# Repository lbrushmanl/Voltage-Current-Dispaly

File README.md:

# Voltage-Current-Dispaly
This project was based around using the 11-digit VFD displays that you can buy for cheap at Jaycar 
https://www.jaycar.co.nz/11-digit-fluoro-display-bargain/p/ZD1880?pos=1&queryId=efb51b3d6997d6bc33e34b690ac22e3b&sort=relevance&searchText=11%20Digit%20Fluoro%20Display%20Bargain

As these displays look cool, I came up with the idea of making a voltage current display that I could then use for lots of my other projects. 
The first 5 digits would be voltage and the last 5 for current leaving the centre one blank.

To drive the display, a voltage of around 4.5V is needed for the filament, and 12V is needed for grids and digits. The 4.5V came from an LM317 adjustable voltage regulator.
The board was designed to use an ATMega8, as I had a few from UNI. 

The display was driven via shift registers and a 7seg decoder, as this would only require three GPIO pins on the MCU to be used. It also seemed like a cool idea.

Due to this driver circuitry, the following data structure was formed.

The first 4 bits are the BCD value that the 7seg decoder will read, the 5th bit is the decimal point, and bits 6 to 15 are the grids of the VFD.
A B C D DP G1 G2 G3 G4 G5 G7 G8 G9 G10 G11

I assembled one board fully and found out that a few things were wrong. I also used my ATMegaU4 dev board for testing rather than the ATMega8, as it was easier to use
The main thing I found wrong was the C segment was connected to the comma. I also found out that the Blanking pin of the decoder was connected high rather than low. The biggest issue was that the display was the wrong way around. Flipping it fixed the problem however it no longer looks as good.

View of the test setup

Initial test after fixing the PCB showing 0 and the dot

The first numbers are quite dim

Finaly brighter and the ADC is conected

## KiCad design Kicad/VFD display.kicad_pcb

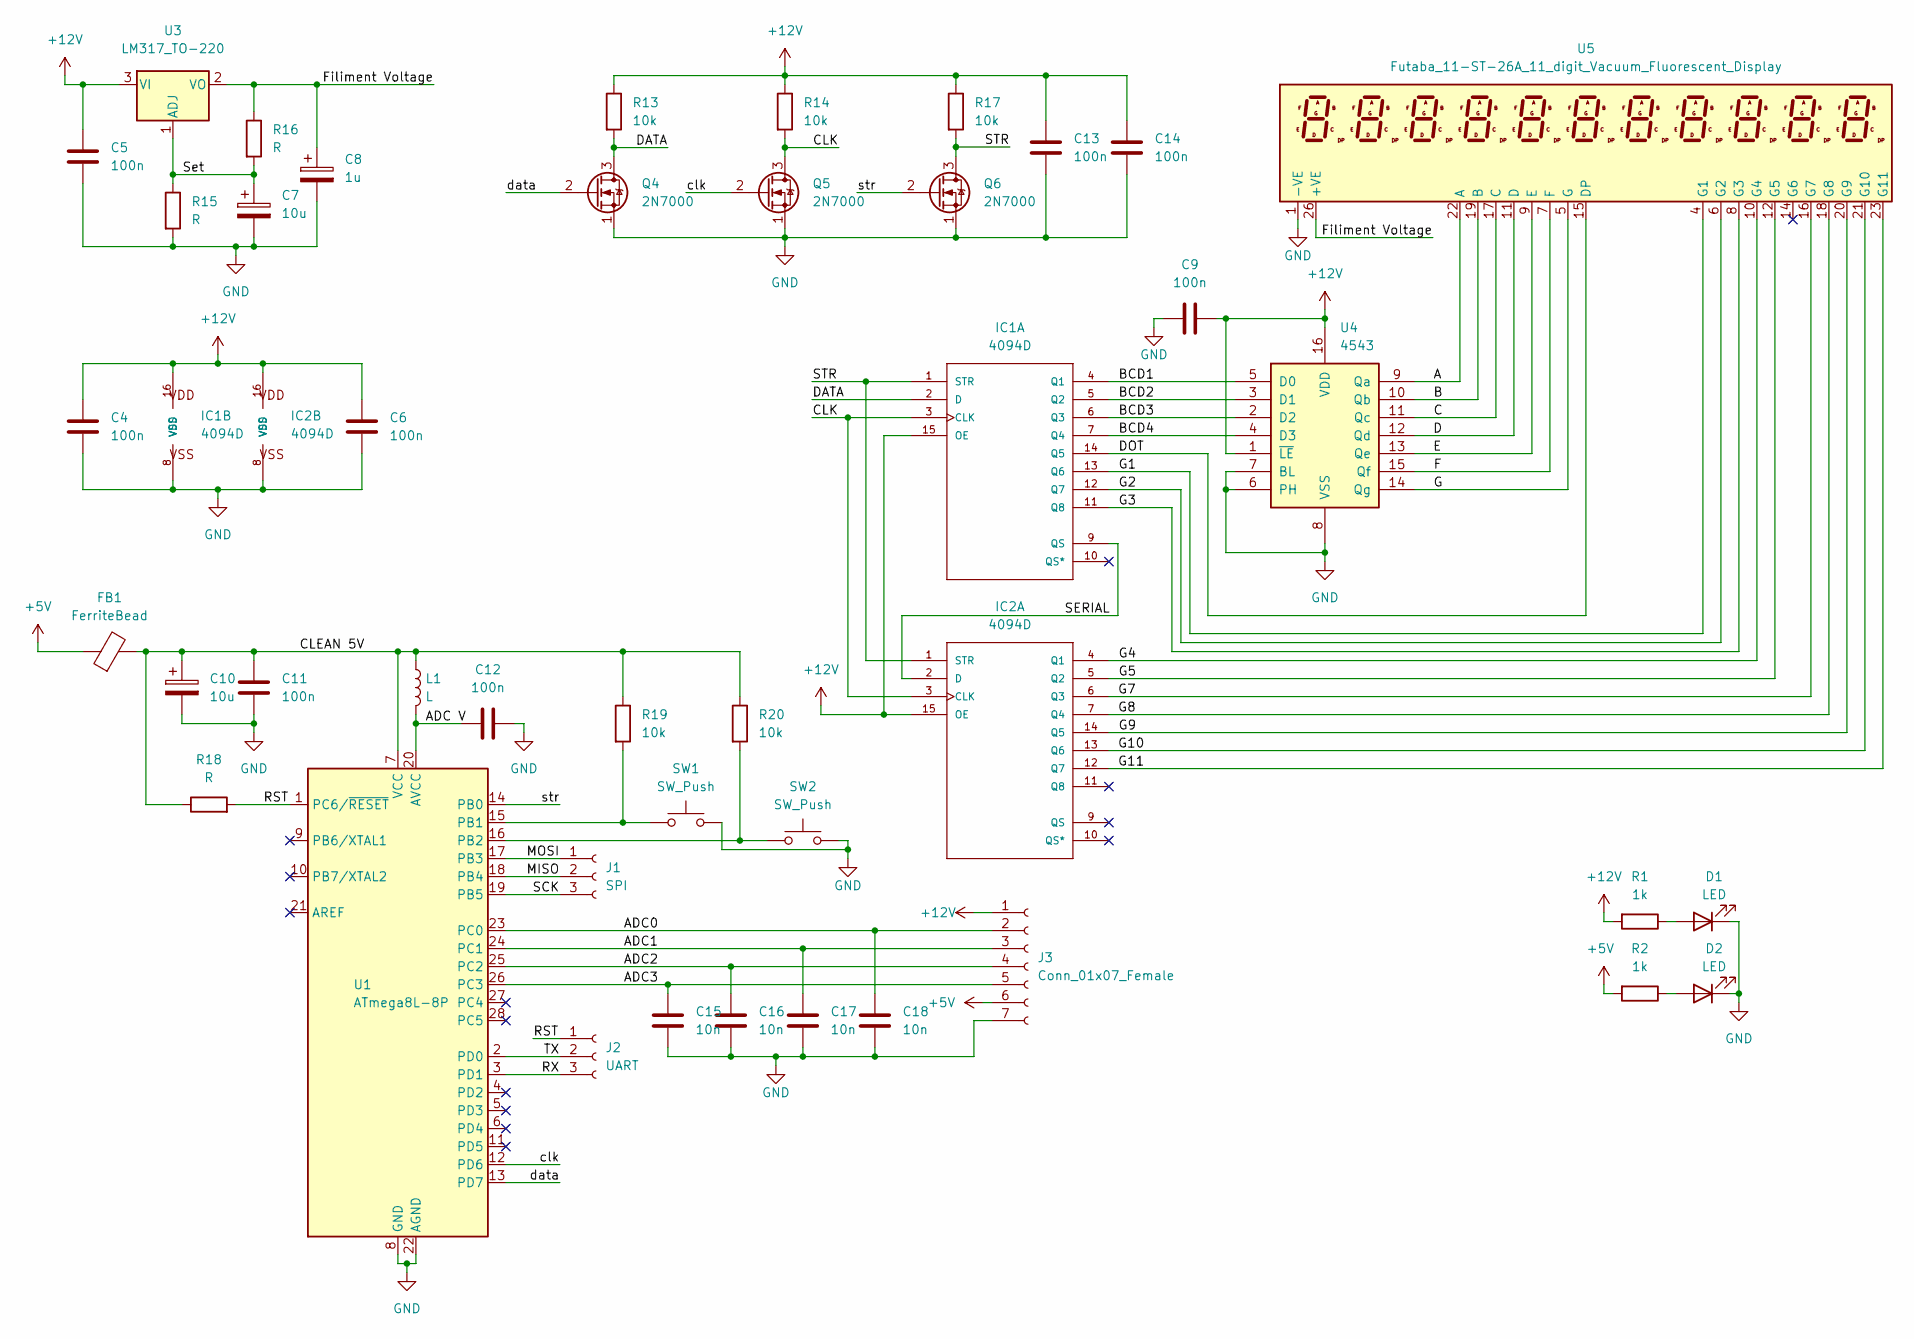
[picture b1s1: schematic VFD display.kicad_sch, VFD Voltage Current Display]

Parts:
C4, C5, C6, C9, C11, C12, C13, C14: 100n; C_Disc_D3.4mm_W2.1mm_P2.50mm
C7, C10: 10u; CP_Radial_D5.0mm_P2.00mm
C8: 1u; CP_Radial_D5.0mm_P2.00mm
C15, C16, C17: 10n; C_Disc_D4.7mm_W2.5mm_P5.00mm
C18: 10n; C_Disc_D3.4mm_W2.1mm_P2.50mm
D1, D2: LED
FB1: FerriteBead; L_0603_1608Metric_Pad1.05x0.95mm_HandSolder
IC1, IC2: 4094D; DIP-16_W7.62mm_LongPads
J1: SPI; PinSocket_1x03_P2.54mm_Vertical
J2: UART; PinSocket_1x03_P2.54mm_Vertical
J3: Conn_01x07_Female; PinSocket_1x07_P2.54mm_Vertical
L1: L; L_0603_1608Metric_Pad1.05x0.95mm_HandSolder
Q4, Q5, Q6: 2N7000; TO-92_Inline_Wide
R1, R2: 1k
R13, R14, R17, R19, R20: 10k; R_Axial_DIN0207_L6.3mm_D2.5mm_P2.54mm_Vertical
R15, R16, R18: R; R_Axial_DIN0207_L6.3mm_D2.5mm_P2.54mm_Vertical
SW1, SW2: SW_Push; SW_PUSH_6mm
U1: ATmega8L-8P; DIP-28_W7.62mm_LongPads
U3: LM317_TO-220; TO-220-3_Vertical
U4: 4543; DIP-16_W7.62mm_LongPads
U5: Futaba_11-ST-26A_11_digit_Vacuum_Fluorescent_Disp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; PinSocket_1x26_P2.54mm_Vertical

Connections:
+5V: FB1.1, J3.6, R2.2
/Display/A: U4.9 (Qa), U5.22 (A)
/Display/ADC0: C18.1, J3.2, U1.23 (PC0)
/Display/ADC1: C17.1, J3.3, U1.24 (PC1)
/Display/ADC2: C16.1, J3.4, U1.25 (PC2)
/Display/ADC3: C15.1, J3.5, U1.26 (PC3)
/Display/ADC V: C12.1, L1.2, U1.20 (AVCC), U1.21 (AREF)
/Display/B: U4.10 (Qb), U5.19 (B)
/Display/BCD1: IC1.4 (Q1), U4.5 (D0)
/Display/BCD2: IC1.5 (Q2), U4.3 (D1)
/Display/BCD3: IC1.6 (Q3), U4.2 (D2)
/Display/BCD4: IC1.7 (Q4), U4.4 (D3)
/Display/C: U4.11 (Qc), U5.13 (C), U5.17 (C)
/Display/CLEAN 5V: C10.1, C11.1, FB1.2, L1.1, R18.1, R19.1, R20.1, U1.7 (VCC)
/Display/CLK: IC1.3 (CLK), IC2.3 (CLK), Q5.3 (D), R14.2
/Display/D: U4.12 (Qd), U5.11 (D)
/Display/DATA: IC1.2 (D), Q4.3 (D), R13.2
/Display/DOT: IC1.14 (Q5), U5.15 (DP)
/Display/E: U4.13 (Qe), U5.9 (E)
/Display/F: U4.15 (Qf), U5.7 (F)
/Display/Filiment Voltage: C8.1, R16.1, U3.2 (VO), U5.26 (+VE)
/Display/G: U4.14 (Qg), U5.5 (G)
/Display/G1: IC1.13 (Q6), U5.4 (G1)
/Display/G2: IC1.12 (Q7), U5.6 (G2)
/Display/G3: IC1.11 (Q8), U5.8 (G3)
/Display/G4: IC2.4 (Q1), U5.10 (G4)
/Display/G5: IC2.5 (Q2), U5.12 (G5)
/Display/G7: IC2.6 (Q3), U5.16 (G7)
/Display/G8: IC2.7 (Q4), U5.18 (G8)
/Display/G9: IC2.14 (Q5), U5.20 (G9)
/Display/G10: IC2.13 (Q6), U5.21 (G10)
/Display/G11: IC2.12 (Q7), U5.23 (G11)
/Display/MISO: J1.2, U1.18 (PB4)
/Display/MOSI: J1.1, U1.17 (PB3)
/Display/RST: J2.1, R18.2, U1.1 (PC6/~RESET)
/Display/RX: J2.3, U1.3 (PD1)
/Display/SCK: J1.3, U1.19 (PB5)
/Display/SERIAL: IC1.9 (QS), IC2.2 (D)
/Display/STR: IC1.1 (STR), IC2.1 (STR), Q6.3 (D), R17.2
/Display/Set: C7.1, R15.1, R16.2, U3.1 (ADJ)
/Display/TX: J2.2, U1.2 (PD0)
/Display/clk: Q5.2 (G), U1.12 (PD6)
/Display/data: Q4.2 (G), U1.13 (PD7)
/Display/str: Q6.2 (G), U1.14 (PB0)
unnamed: D1.2 (A), R1.1
unnamed: D2.2 (A), R2.1
unnamed: R19.2, SW1.1, U1.15 (PB1)
unnamed: R20.2, SW2.1, U1.16 (PB2)

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
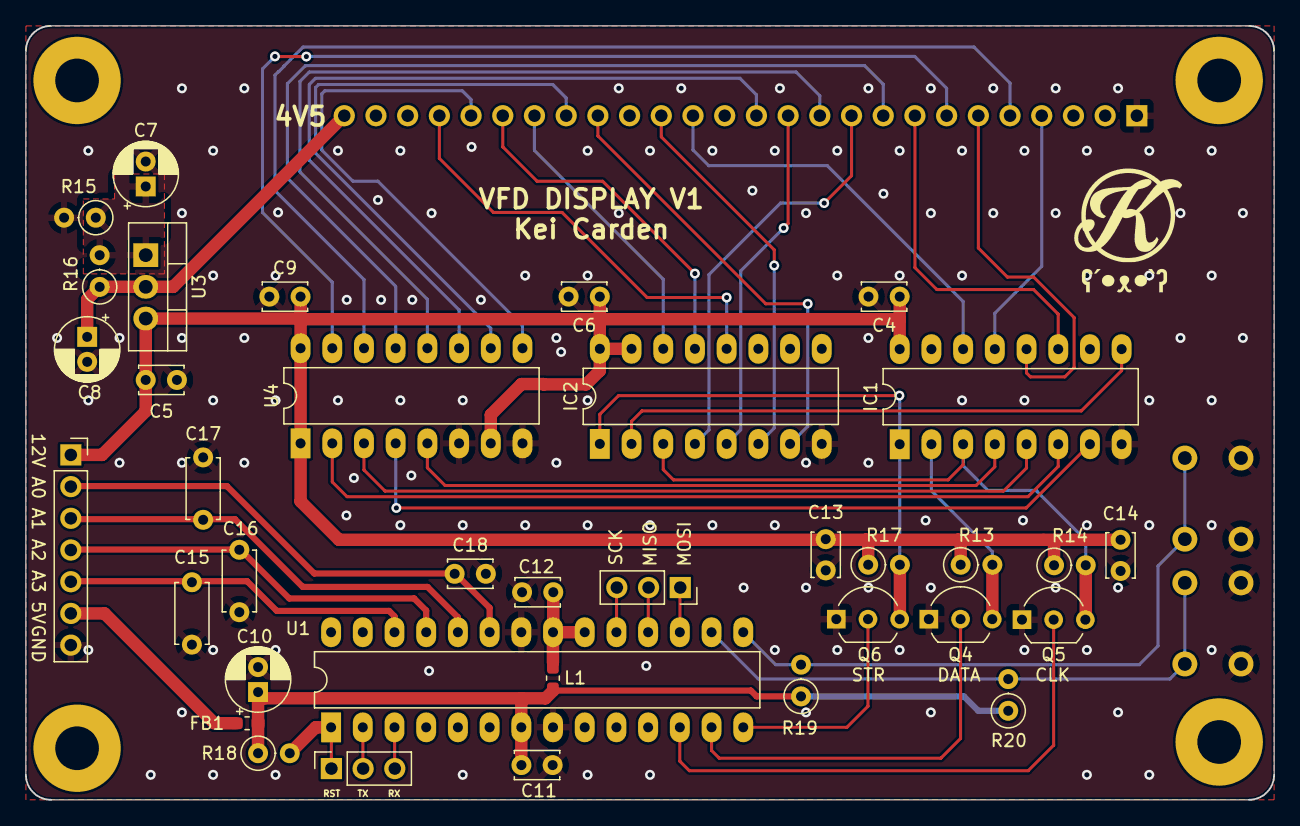
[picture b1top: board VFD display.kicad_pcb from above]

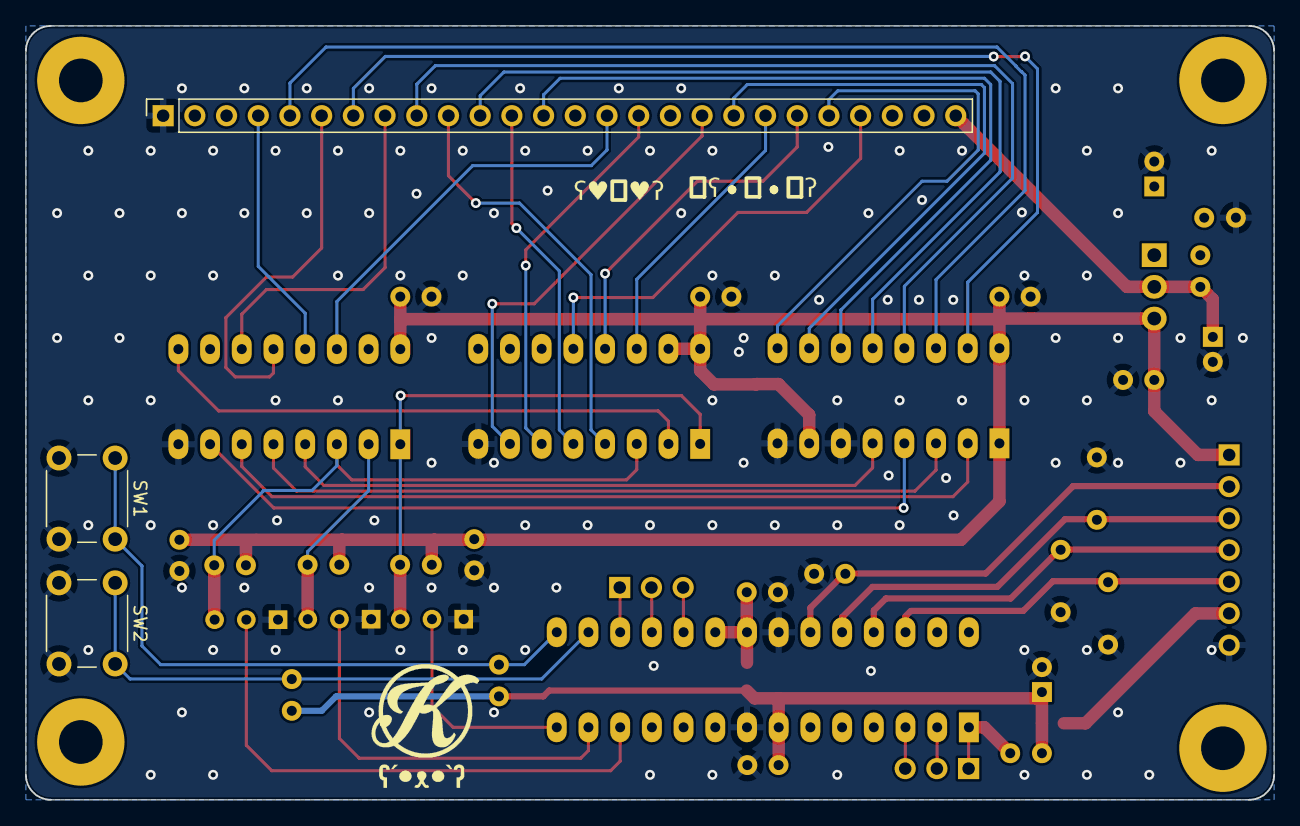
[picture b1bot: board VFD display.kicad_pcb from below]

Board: 2 copper layers, 100.0 x 62.0 mm, 39 parts (3 on the bottom side), 48 nets.

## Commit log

2023-01-30 Og VFD project
2023-01-30 V2 Schematic updates added indication LEDs for 12V and 5V, fixed the display symbol so C is connected to pin 17, added values to the capacitors on the ADC lines, removed voltage from AREF.
2023-02-16 Added VFD test code
